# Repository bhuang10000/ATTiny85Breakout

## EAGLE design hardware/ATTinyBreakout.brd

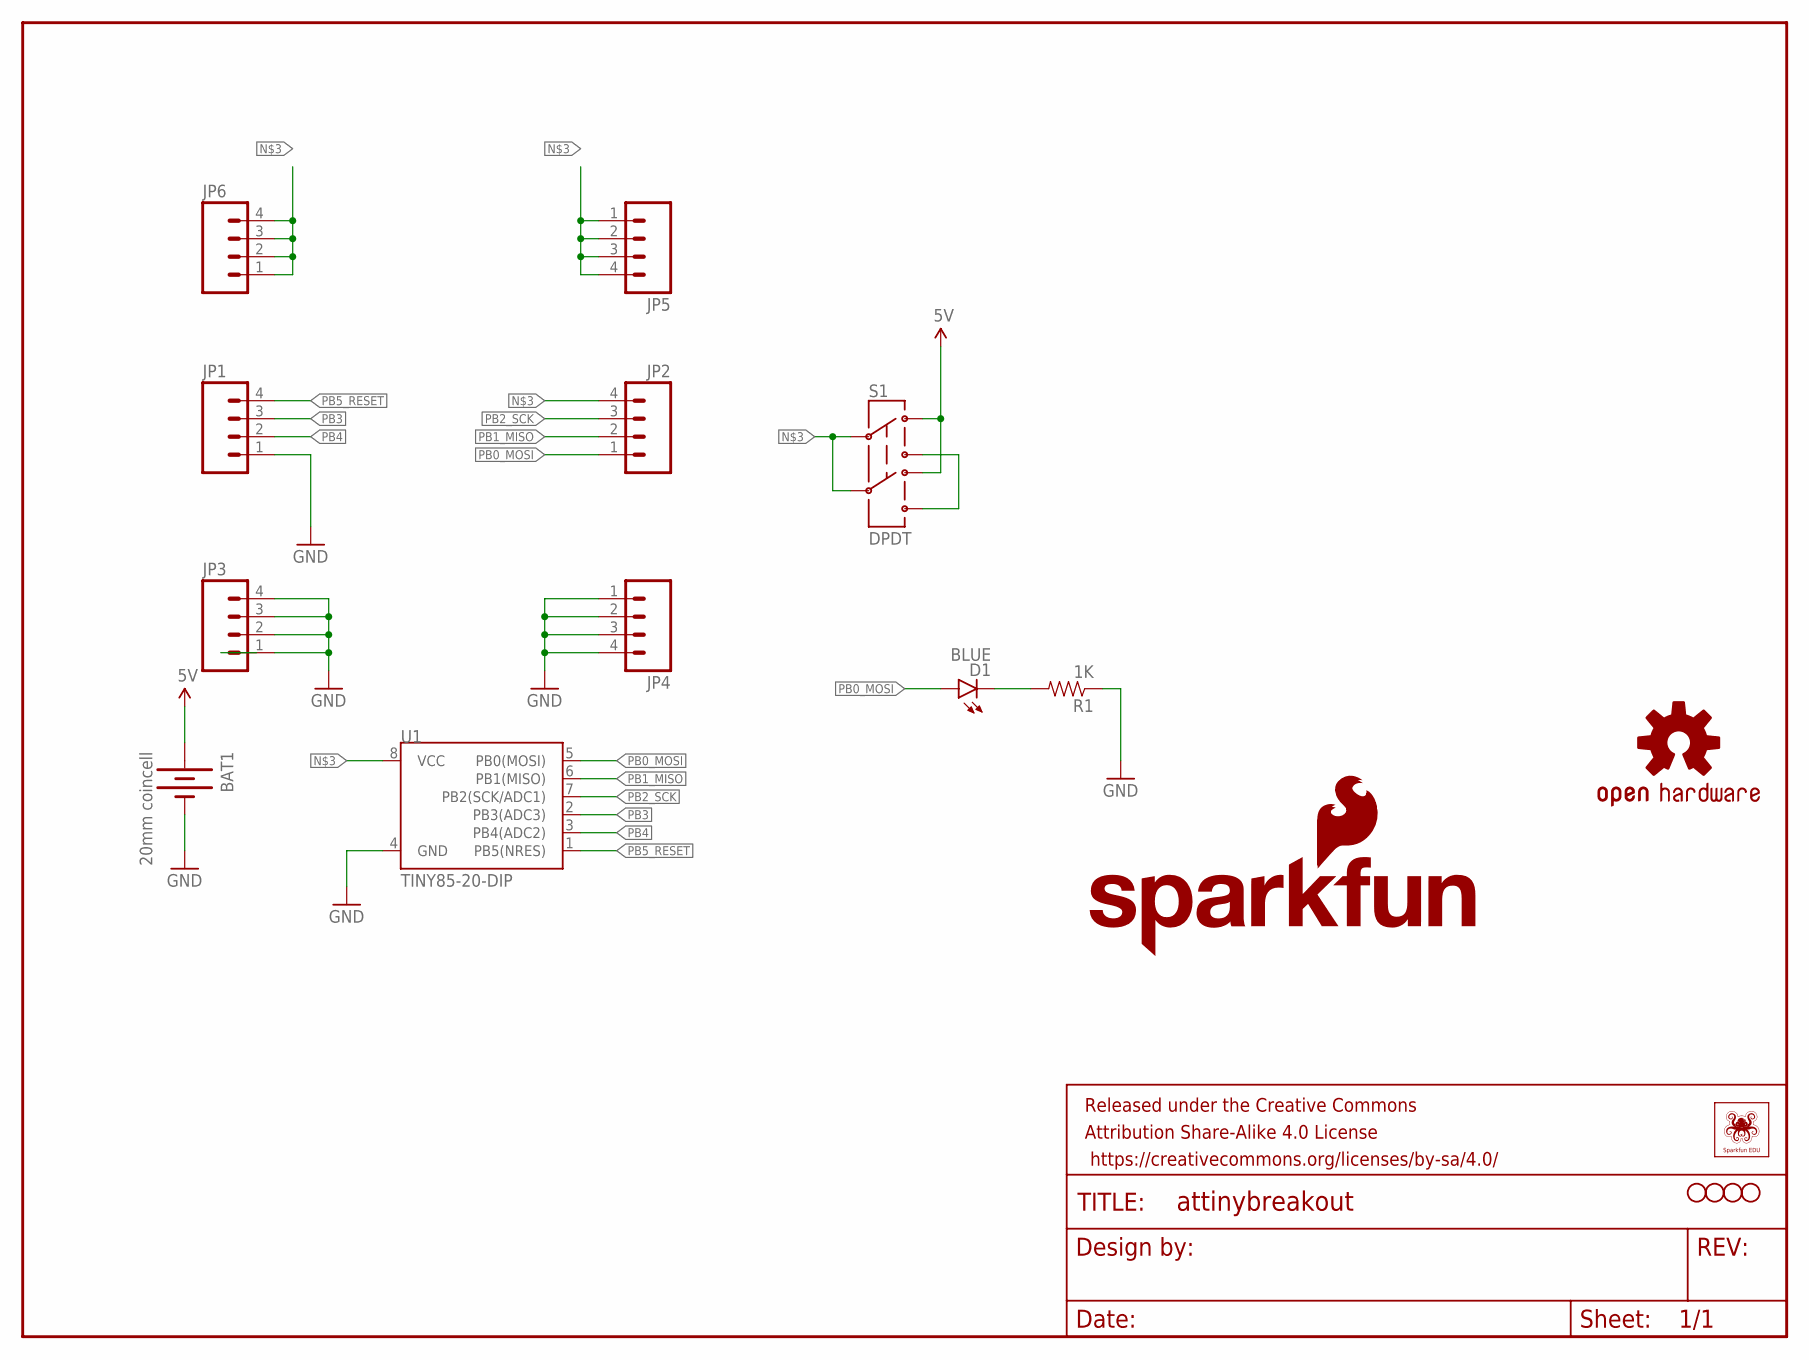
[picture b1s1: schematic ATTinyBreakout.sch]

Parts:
BAT1: 20mm coincell; BATTCON_20MM_4LEGS
D1: BLUE; LED-1206
FRAME1: FRAME-LETTER; CREATIVE_COMMONS
JP1, JP2, JP3, JP4, JP5, JP6: M04LOCK; 1X04_LOCK
LOGO2: SFE_LOGO_FLAME.1_INCH; SFE_LOGO_FLAME_.1
LOGO3: OSHW-LOGOS; OSHW-LOGO-S
LOGO4: SFE_LOGO_NAME_FLAME.1_INCH; SFE_LOGO_NAME_FLAME_.1
R1: 1K; 0603-RES
S1: DPDT; AYZ0202
STANDOFF1, STANDOFF2, STANDOFF3, STANDOFF4: STAND-OFF
U1: TINY85-20-DIP; DIP08
U$2: SFE_LUDUSSFE_LUDUS-M; SFE_LUDUS-M

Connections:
GND: BAT1.2 (-), JP1.1, JP3.1, JP3.2, JP3.3, JP3.4, JP4.1, JP4.2, JP4.3, JP4.4, R1.1, U1.4 (GND)
unnamed: D1.C, R1.2
unnamed: S1.3, S1.6
unnamed: JP2.4, JP5.1, JP5.2, JP5.3, JP5.4, JP6.1, JP6.2, JP6.3, JP6.4, S1.2, S1.5, U1.8 (VCC)
PB0_MOSI: D1.A, JP2.1, U1.5 (PB0(MOSI))
PB1_MISO: JP2.2, U1.6 (PB1(MISO))
PB2_SCK: JP2.3, U1.7 (PB2(SCK/ADC1))
PB3: JP1.3, U1.2 (PB3(ADC3))
PB4: JP1.2, U1.3 (PB4(ADC2))
PB5_RESET: JP1.4, U1.1 (PB5(NRES))
VCC: BAT1.1 (+), S1.1, S1.4

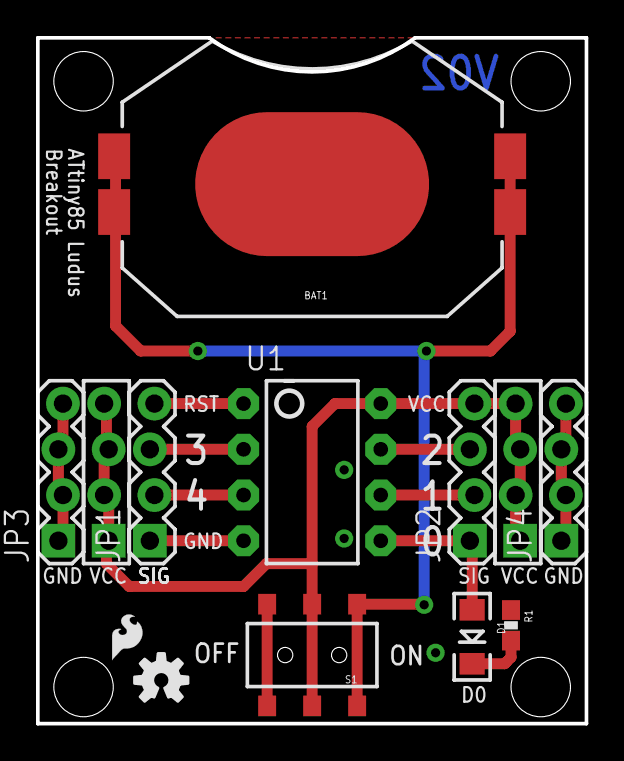
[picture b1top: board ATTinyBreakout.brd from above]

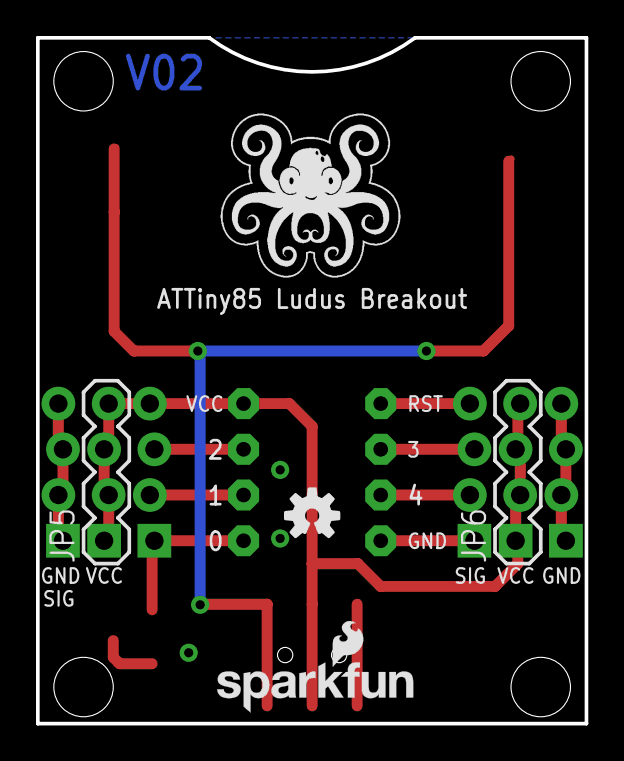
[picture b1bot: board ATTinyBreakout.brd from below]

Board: 2 copper layers, 30.5 x 38.1 mm, 21 parts (5 on the bottom side), 11 nets.

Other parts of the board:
U$1: OSHW-LOGOS; OSHW-LOGO-S

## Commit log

2015-04-28 Revision with 3 pin headers (Ludus style)

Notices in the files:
parts and their libraries:
SparkFun-Electromechanical: Licensing: Creative Commons ShareAlike 4.0 International - https://creativecommons.org/licenses/by-sa/4.0
SparkFun-Aesthetics: Released under the Creative Commons Attribution Share-Alike 4.0 License
SparkFun-Aesthetics: https://creativecommons.org/licenses/by-sa/4.0
